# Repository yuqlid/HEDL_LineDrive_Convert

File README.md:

# HEDL_LineDrive_Convert
HEDL-5xxx HEDL-9xxx Encoder にて出力される差動のエンコーダパルスをマイコンで読めるように複合する基板

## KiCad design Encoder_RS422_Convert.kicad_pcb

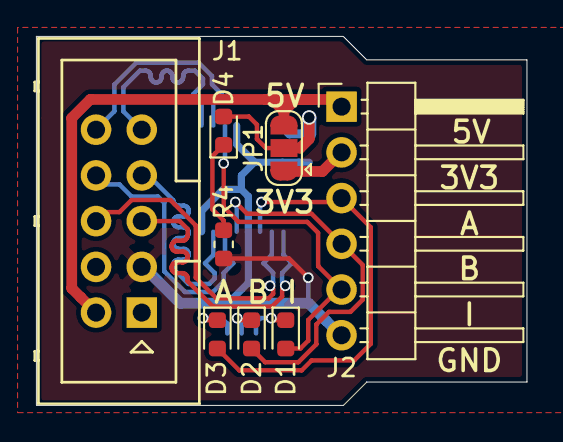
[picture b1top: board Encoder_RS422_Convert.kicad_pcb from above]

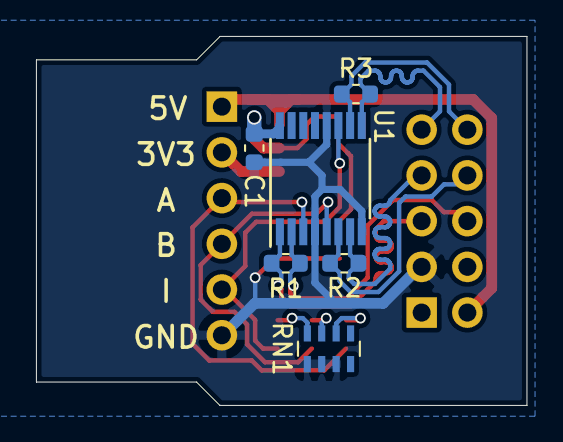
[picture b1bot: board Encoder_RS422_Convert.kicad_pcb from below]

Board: 2 copper layers, 27.2 x 20.5 mm, 14 parts (6 on the bottom side), 17 nets.

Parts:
C1: C; C_0603_1608Metric
D1, D2, D3, D4: LED; LED_0603_1608Metric
J1: Conn_02x05_Odd_Even; Multicomp_MC9A12-1034_2x05_P2.54mm_Vertical
J2: Conn_01x06; PinHeader_1x06_P2.54mm_Horizontal
JP1: Jumper_3_Open; SolderJumper-3_P1.3mm_Open_RoundedPad1.0x1.5mm
R1, R2, R3: 120; R_0603_1608Metric
R4: 1k; R_0603_1608Metric
RN1: R_Pack04; R_Array_Concave_4x0603
U1: AM26LV32xD; TSSOP-16_4.4x5mm_P0.65mm

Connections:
+3V3: J2.2, JP1.1
+5V: J1.2, J2.1, JP1.3
/A: D3.2, J2.3, U1.3
/A+: J1.6, R1.1, U1.2
/A-: J1.5, R1.2, U1.1
/B: D2.2, J2.4, U1.5
/B+: J1.8, R2.1, U1.6
/B-: J1.7, R2.2, U1.7
/I: D1.2, J2.5, U1.11
/I+: J1.10, R3.1, U1.10
/I-: J1.9, R3.2, U1.9
GND: C1.2, J1.3, J2.6, R4.2, RN1.1, RN1.2, RN1.3, U1.4, U1.8, U1.12
unnamed: C1.1, D4.2, JP1.2, U1.16
unnamed: D1.1, RN1.8
unnamed: D2.1, RN1.7
unnamed: D3.1, RN1.6
unnamed: D4.1, R4.1

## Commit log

2019-11-27 Add KIcad files
